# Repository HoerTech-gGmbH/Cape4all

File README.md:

# Cape4all
Open Hardware Multichannel Sound Interface for Hearing Aid Research on Beaglebone Black

### Hardware Design Files

The published Beaglebone AD/DA Cape schematic and board layout files were developed
by the Institute of Microelectronic Systems at Leibniz Universität Hannover together
with the Videantis GmbH within DFG Cluster of Excellence EXC 1077/1 "Hearing4all".
They are published under the CC BY-NC-SA 4.0 license.

### Kernel Driver Files

These were developed by 64Studio for HörTech gGmbH. They are published under the
GPLv2 license.

See the respective directories for the full license text.

## Publication

Cape4all is described in a contribution to the Linux Audio Conference, see [LAC2018_Cape4all.pdf](LAC2018_Cape4all.pdf). 

If you want to refer to Cape4all in a publication, please cite

Herzke, T., Kayser H., Seifert, C., Maanen, P., Obbard, C., Payá-Vayá, G., Blume, H., 
Hohmann, V., “Open Hardware Multichannel Sound Interface for Hearing Aid Research on 
BeagleBone Black with openMHA: Cape4all,” Linux Audio Conference (LAC2018), May 09, 
Berlin, Germany, 2018.

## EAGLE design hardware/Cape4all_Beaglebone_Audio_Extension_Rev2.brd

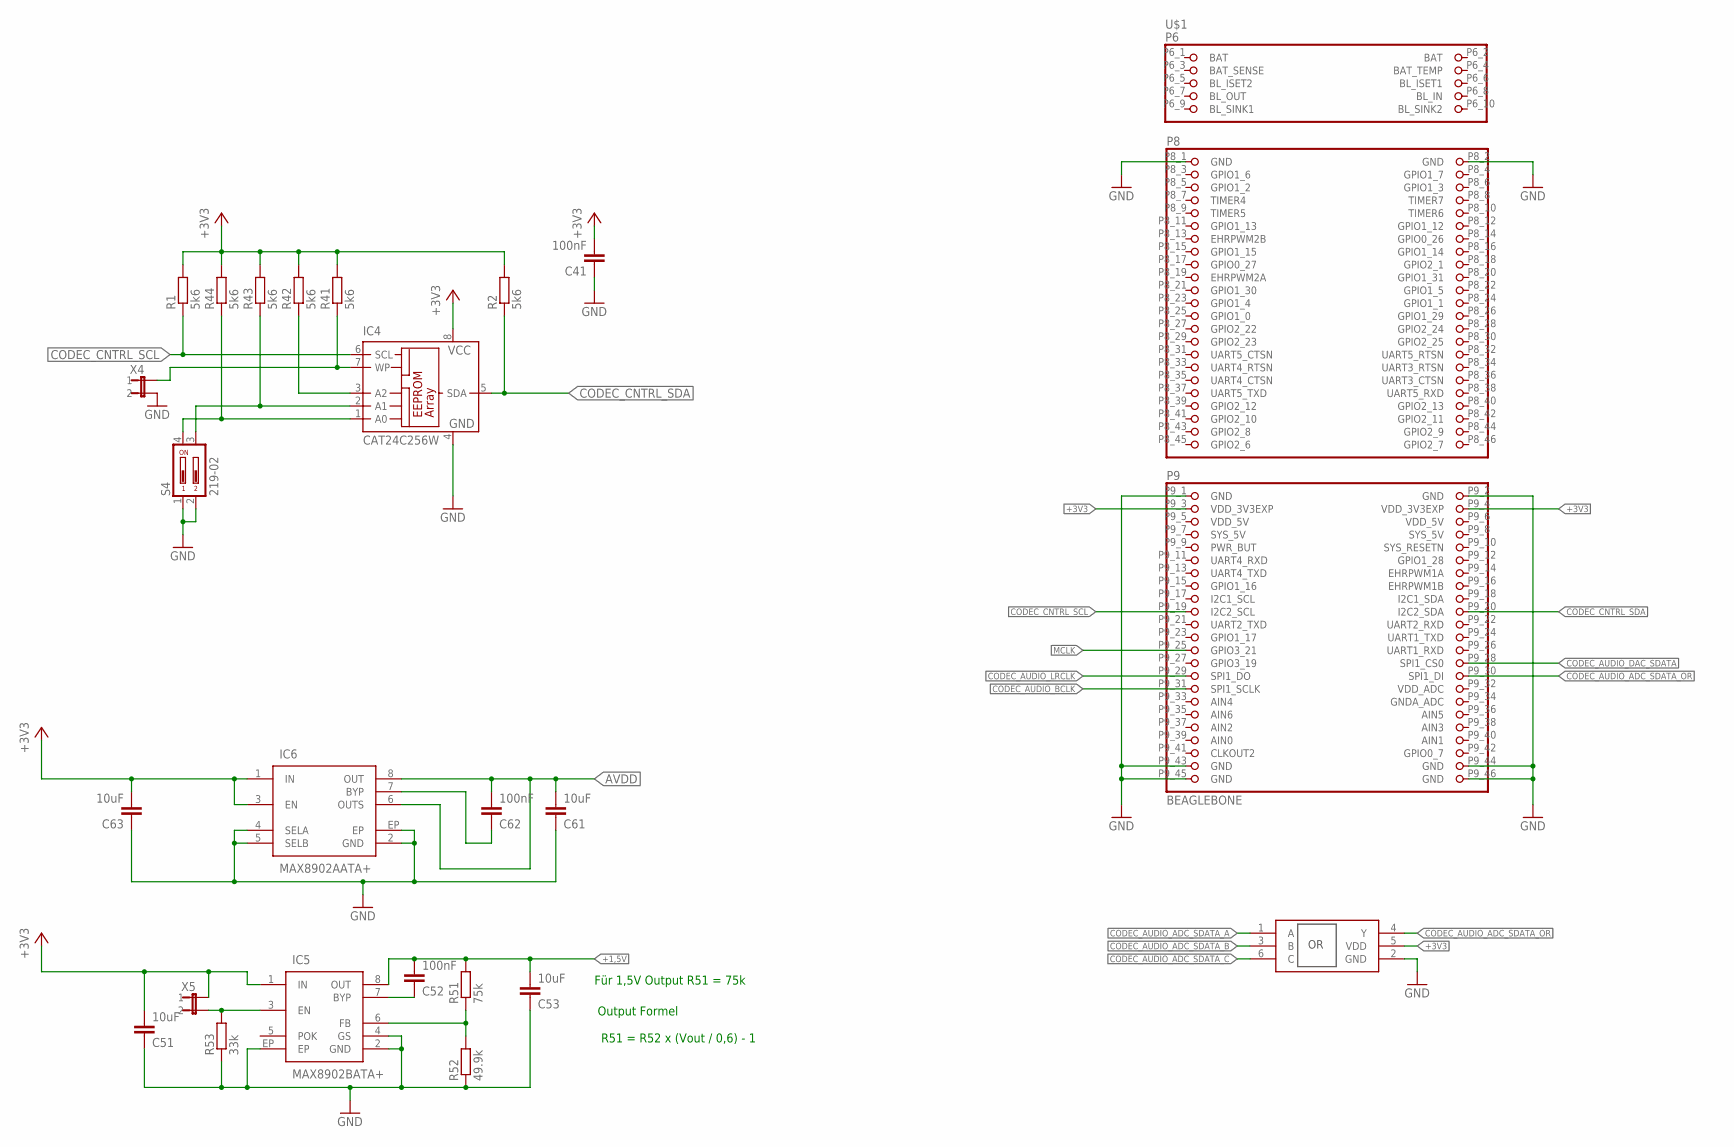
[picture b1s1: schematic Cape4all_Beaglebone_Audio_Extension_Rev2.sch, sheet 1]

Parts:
C41, C52, C62: 100nF; C0603
C51, C53, C61, C63: 10uF; C0603
IC4: CAT24C256W; SO-08
IC5: MAX8902BATA+; 8-TDFN-EP
IC6: MAX8902AATA+; 8-TDFN-EP
IC7: SN74LVC1G332SMD; SOT23-6L
R1, R2, R41, R42, R43, R44: 5k6; R0603
R51: 75k; R0603
R52: 49.9k; R0603
R53: 33k; R0603
S4: 219-02; CTS-219-02
U$1: BEAGLEBONE
X4, X5: JP1X2

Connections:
+1,5V: C52.2, C53.2, IC5.8 (OUT), R51.2; also elsewhere on the board
+3V3: C41.2, C51.2, C63.2, IC4.8 (VCC), IC5.1 (IN), IC6.1 (IN), IC6.3 (EN), IC7.5 (VDD), R1.2, R2.2, R41.2, R42.2, R43.2, R44.2, U$1.P9_3 (VDD_3V3EXP), U$1.P9_4 (VDD_3V3EXP), X5.1; also elsewhere on the board
AVDD: C61.2, C62.2, IC6.6 (OUTS), IC6.8 (OUT); also elsewhere on the board
CODEC_AUDIO_ADC_SDATA_A: IC7.1 (A); also elsewhere on the board
CODEC_AUDIO_ADC_SDATA_B: IC7.3 (B); also elsewhere on the board
CODEC_AUDIO_ADC_SDATA_C: IC7.6 (C); also elsewhere on the board
CODEC_AUDIO_ADC_SDATA_OR: IC7.4 (Y), U$1.P9_30 (SPI1_DI)
CODEC_AUDIO_BCLK: U$1.P9_31 (SPI1_SCLK); also elsewhere on the board
CODEC_AUDIO_DAC_SDATA: U$1.P9_28 (SPI1_CS0); also elsewhere on the board
CODEC_AUDIO_LRCLK: U$1.P9_29 (SPI1_DO); also elsewhere on the board
CODEC_CNTRL_SCL: IC4.6 (SCL), R1.1, U$1.P9_19 (I2C2_SCL); also elsewhere on the board
CODEC_CNTRL_SDA: IC4.5 (SDA), R2.1, U$1.P9_20 (I2C2_SDA); also elsewhere on the board
GND: C41.1, C51.1, C53.1, C61.1, C63.1, IC4.4 (GND), IC5.2 (GND), IC5.4 (GS), IC5.EP, IC6.2 (GND), IC6.4 (SELA), IC6.5 (SELB), IC6.EP, IC7.2 (GND), R52.1, R53.1, S4.1, S4.2, U$1.P8_1 (GND), U$1.P8_2 (GND), U$1.P9_1 (GND), U$1.P9_2 (GND), U$1.P9_43 (GND), U$1.P9_44 (GND), U$1.P9_45 (GND), U$1.P9_46 (GND), X4.2; also elsewhere on the board
MCLK: U$1.P9_25 (GPIO3_21); also elsewhere on the board
unnamed: IC5.3 (EN), R53.2, X5.2
unnamed: IC4.3 (A2), R42.1
unnamed: IC4.2 (A1), R43.1, S4.3
unnamed: IC4.1 (A0), R44.1, S4.4
unnamed: IC4.7 (WP), R41.1, X4.1
unnamed: C52.1, IC5.7 (BYP)
unnamed: IC5.6 (FB), R51.1, R52.2
unnamed: C62.1, IC6.7 (BYP)

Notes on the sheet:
Für 1,5V Output R51 = 75k
Output Formel R51 = R52 x (Vout / 0,6) - 1

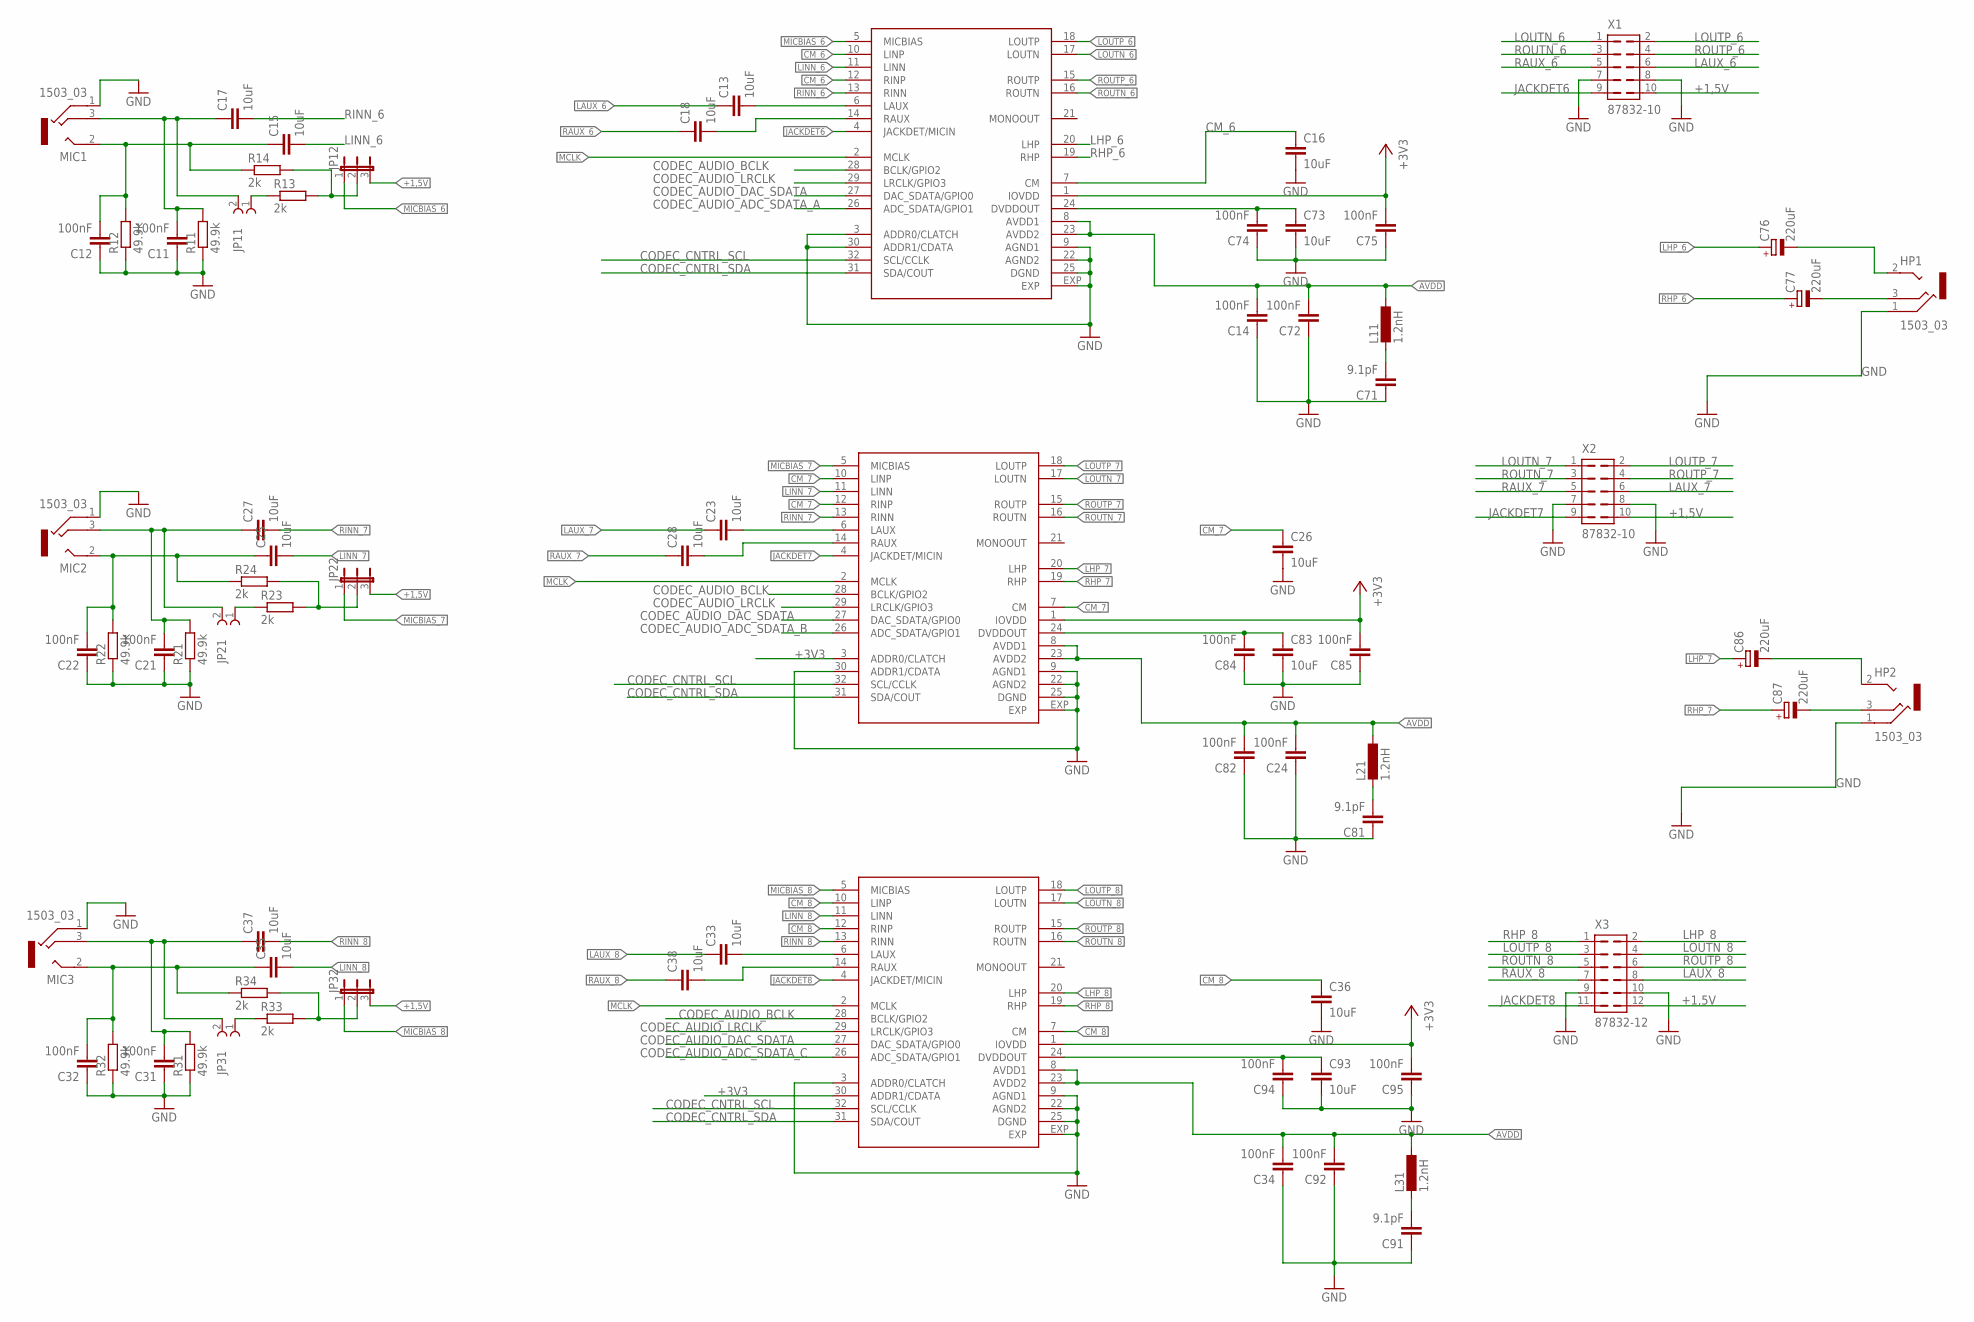
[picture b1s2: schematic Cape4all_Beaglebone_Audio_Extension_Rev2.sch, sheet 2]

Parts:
C11, C12, C14, C21, C22, C24, C31, C32, C34, C72, C74, C75, C82, C84, C85, C92, C94, C95: 100nF; C0603
C13, C15, C16, C17, C18, C23, C25, C26, C27, C28, C33, C35, C36, C37, C38, C73, C83, C93: 10uF; C0603
C71, C81, C91: 9.1pF; C0603
C76, C77, C86, C87: 220uF; B/3528-21R
HP1, HP2: 1503_03
IC1, IC2, IC3: ADAU1761BCPZ; LFCSP32
JP11, JP21, JP31: 62000211121
JP12, JP22, JP32: JP1X3
L11, L21, L31: 1.2nH; R0603
MIC1, MIC2, MIC3: 1503_03
R11, R12, R21, R22, R31, R32: 49.9k; R0603
R13, R14, R23, R24, R33, R34: 2k; R0603
X1, X2: 87832-10
X3: 87832-12

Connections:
+1,5V: JP12.3, JP22.3, JP32.3, X1.10, X2.10, X3.12; also elsewhere on the board
+3V3: C75.2, C85.2, C95.2, IC1.1 (IOVDD), IC2.1 (IOVDD), IC2.3 (ADDR0/CLATCH), IC3.1 (IOVDD), IC3.30 (ADDR1/CDATA); also elsewhere on the board
AVDD: C14.2, C24.2, C34.2, C72.2, C82.2, C92.2, IC1.8 (AVDD1), IC1.23 (AVDD2), IC2.8 (AVDD1), IC2.23 (AVDD2), IC3.8 (AVDD1), IC3.23 (AVDD2), L11.1, L21.1, L31.1; also elsewhere on the board
CM_6: C16.1, IC1.7 (CM), IC1.10 (LINP), IC1.12 (RINP)
CM_7: C26.1, IC2.7 (CM), IC2.10 (LINP), IC2.12 (RINP)
CM_8: C36.1, IC3.7 (CM), IC3.10 (LINP), IC3.12 (RINP)
CODEC_AUDIO_ADC_SDATA_A: IC1.26 (ADC_SDATA/GPIO1); also elsewhere on the board
CODEC_AUDIO_ADC_SDATA_B: IC2.26 (ADC_SDATA/GPIO1); also elsewhere on the board
CODEC_AUDIO_ADC_SDATA_C: IC3.26 (ADC_SDATA/GPIO1); also elsewhere on the board
CODEC_AUDIO_BCLK: IC1.28 (BCLK/GPIO2), IC2.28 (BCLK/GPIO2), IC3.28 (BCLK/GPIO2); also elsewhere on the board
CODEC_AUDIO_DAC_SDATA: IC1.27 (DAC_SDATA/GPIO0), IC2.27 (DAC_SDATA/GPIO0), IC3.27 (DAC_SDATA/GPIO0); also elsewhere on the board
CODEC_AUDIO_LRCLK: IC1.29 (LRCLK/GPIO3), IC2.29 (LRCLK/GPIO3), IC3.29 (LRCLK/GPIO3); also elsewhere on the board
CODEC_CNTRL_SCL: IC1.32 (SCL/CCLK), IC2.32 (SCL/CCLK), IC3.32 (SCL/CCLK); also elsewhere on the board
CODEC_CNTRL_SDA: IC1.31 (SDA/COUT), IC2.31 (SDA/COUT), IC3.31 (SDA/COUT); also elsewhere on the board
DVDDOUT_6: C73.1, C74.2, IC1.24 (DVDDOUT)
DVDDOUT_7: C83.1, C84.2, IC2.24 (DVDDOUT)
DVDDOUT_8: C93.1, C94.2, IC3.24 (DVDDOUT)
GND: C11.1, C12.1, C14.1, C16.2, C21.1, C22.1, C24.1, C26.2, C31.1, C32.1, C34.1, C36.2, C71.1, C72.1, C73.2, C74.1, C75.1, C81.1, C82.1, C83.2, C84.1, C85.1, C91.1, C92.1, C93.2, C94.1, C95.1, HP1.1, HP2.1, IC1.3 (ADDR0/CLATCH), IC1.9 (AGND1), IC1.22 (AGND2), IC1.25 (DGND), IC1.30 (ADDR1/CDATA), IC1.EXP, IC2.9 (AGND1), IC2.22 (AGND2), IC2.25 (DGND), IC2.30 (ADDR1/CDATA), IC2.EXP, IC3.3 (ADDR0/CLATCH), IC3.9 (AGND1), IC3.22 (AGND2), IC3.25 (DGND), IC3.EXP, MIC1.1, MIC2.1, MIC3.1, R11.1, R12.1, R21.1, R22.1, R31.1, R32.1, X1.7, X1.8, X2.7, X2.8, X3.9, X3.10; also elsewhere on the board
JACKDET6: IC1.4 (JACKDET/MICIN), X1.9
JACKDET7: IC2.4 (JACKDET/MICIN), X2.9
JACKDET8: IC3.4 (JACKDET/MICIN), X3.11
LAUX_6: C13.1, X1.6
LAUX_7: C23.1, X2.6
LAUX_8: C33.1, X3.8
LHP_6: C76.+, IC1.20 (LHP)
LHP_7: C86.+, IC2.20 (LHP)
LHP_8: IC3.20 (LHP), X3.2
LINN_6: C15.2, IC1.11 (LINN)
LINN_7: C25.2, IC2.11 (LINN)
LINN_8: C35.2, IC3.11 (LINN)
LOUTN_6: IC1.17 (LOUTN), X1.1
LOUTN_7: IC2.17 (LOUTN), X2.1
LOUTN_8: IC3.17 (LOUTN), X3.4
LOUTP_6: IC1.18 (LOUTP), X1.2
LOUTP_7: IC2.18 (LOUTP), X2.2
LOUTP_8: IC3.18 (LOUTP), X3.3
MCLK: IC1.2 (MCLK), IC2.2 (MCLK), IC3.2 (MCLK); also elsewhere on the board
MIC1L: C12.2, C15.1, MIC1.2, R12.2, R14.1
MIC1R: C11.2, C17.1, JP11.2 (1), MIC1.3, R11.2
MIC2L: C22.2, C25.1, MIC2.2, R22.2, R24.1
MIC2R: C21.2, C27.1, JP21.2 (1), MIC2.3, R21.2
MIC3L: C32.2, C35.1, MIC3.2, R32.2, R34.1
MIC3R: C31.2, C37.1, JP31.2 (1), MIC3.3, R31.2
MICBIAS_6: IC1.5 (MICBIAS), JP12.1
MICBIAS_7: IC2.5 (MICBIAS), JP22.1
MICBIAS_8: IC3.5 (MICBIAS), JP32.1
unnamed: C91.2, L31.2
unnamed: C71.2, L11.2
unnamed: C23.2, IC2.6 (LAUX)
unnamed: C28.2, IC2.14 (RAUX)
unnamed: C13.2, IC1.6 (LAUX)
unnamed: C18.2, IC1.14 (RAUX)
unnamed: C33.2, IC3.6 (LAUX)
unnamed: C38.2, IC3.14 (RAUX)
unnamed: JP11.1 (2), R13.1
unnamed: JP21.1 (2), R23.1
unnamed: JP31.1 (2), R33.1
unnamed: JP32.2, R33.2, R34.2
unnamed: JP12.2, R13.2, R14.2
unnamed: JP22.2, R23.2, R24.2
unnamed: C87.-, HP2.3
unnamed: C86.-, HP2.2
unnamed: C81.2, L21.2
unnamed: C77.-, HP1.3
unnamed: C76.-, HP1.2
RAUX_6: C18.1, X1.5
RAUX_7: C28.1, X2.5
RAUX_8: C38.1, X3.7
RHP_6: C77.+, IC1.19 (RHP)
RHP_7: C87.+, IC2.19 (RHP)
RHP_8: IC3.19 (RHP), X3.1
RINN_6: C17.2, IC1.13 (RINN)
RINN_7: C27.2, IC2.13 (RINN)
RINN_8: C37.2, IC3.13 (RINN)
ROUTN_6: IC1.16 (ROUTN), X1.3
ROUTN_7: IC2.16 (ROUTN), X2.3
ROUTN_8: IC3.16 (ROUTN), X3.5
ROUTP_6: IC1.15 (ROUTP), X1.4
ROUTP_7: IC2.15 (ROUTP), X2.4
ROUTP_8: IC3.15 (ROUTP), X3.6

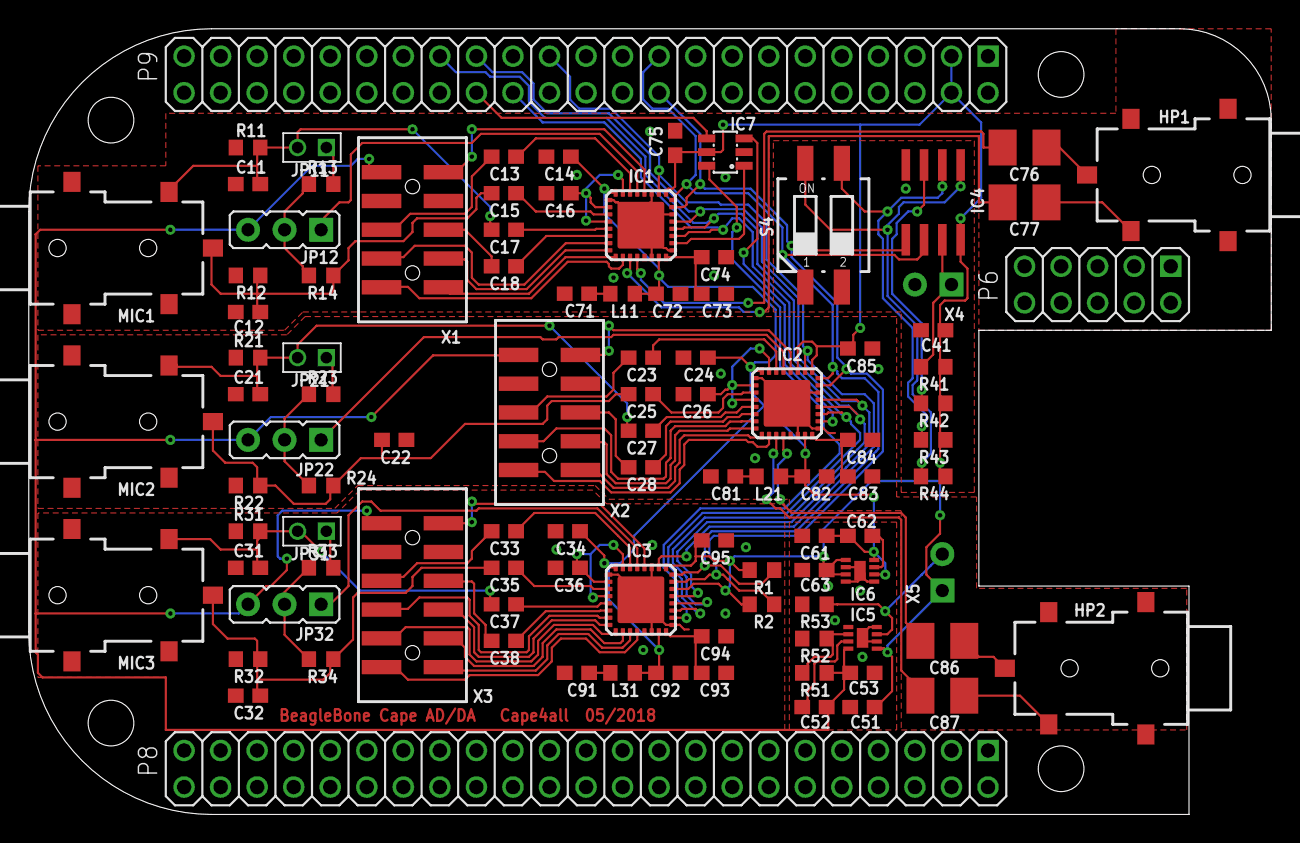
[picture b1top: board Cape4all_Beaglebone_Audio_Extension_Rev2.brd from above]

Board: 4 copper layers, 86.4 x 54.6 mm, 99 parts (0 on the bottom side), 89 nets.

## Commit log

2018-03-29 Change license info to GPL v2 or later.
    There was an error in the lines before the patch stating license was GPL 3 or later.
    It is really GPL 2 or later.
2018-03-30 Add reference manual for Cape4all hardware.
2018-04-11 Add EEPROM content
2020-05-01 Replace outdated instructions
2020-07-01 Revised hardware layout files with microphone voltage supply set to 1.5V, missing jumpers added.
2020-07-03 add LAC2018 paper

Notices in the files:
parts and their libraries:
EAGLE-BOARD-TO-BOARD_CONNECTORS-rev17a: Copyright: Würth Elektronik
